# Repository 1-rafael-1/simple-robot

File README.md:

# simple-robot

A not-too-simple tracked robot with autonomous navigation and sensor-driven obstacle avoidance, written in Rust with Embassy. v2 reached the limits of its hardware platform; development continues in the follow-up [explorer-robot](https://github.com/1-rafael-1/explorer-robot) repository.

*Side view showing the robot's profile — the v2 iteration.*

## Project History

This started out as a hobby project for my 10-year-old son, who wanted me to build a robot for him. The thing started as a rather simple machine (v1) and then I got a little carried away. Check out the v1-robot navigating autonomously, download the demo video here: [Autonomous Operation](misc/media/autonomous-mode.mp4).

> Note: The initial version of this robot is preserved in the [`v1` tag](../../tree/v1). That version represents a simple but functional obstacle-avoiding robot using basic components. The v2 iteration described here is tagged [`v2`](../../tree/v2) and is now mothballed.

In v1, the robot could move autonomously by avoiding obstacles in a very simple way. That meant driving straight until an obstacle is detected, back up a little and then make a random turn. It was fun to watch and my son was happy with it.

v2 set out to be much more capable. The plan was to add spatial awareness through an IMU and a sweeping ultrasonic sensor, build more sophisticated autonomous navigation modes, and eventually integrate an AI camera module for follow-me and object-finding. Some of that worked out; some of it ran into hardware limits that couldn't be solved on this platform.

People have pointed out to me various things. The gist is that there are of course ready-made chassis solutions, ready-made RTOS for robotics and even probably complete systems available and that I am setting out to solve things that can be solved with much less effort by using existing things in code as well as hardware. This is all true and I do not dispute it. My motivation is different, though: I am not truly that much interested in having the actual robot, I have no use case at all for it, in fact. I just truly enjoy the process of building, figuring out how to do things, learning a ton of new stuff and it passes my rare spare time in a rewarding way.

## What v2 Achieved

The v2 firmware is a fully integrated platform built on Embassy async with a task-oriented architecture. A central orchestrator runs an event loop, dispatching sensor events to behavior handlers and UI updates. The drive subsystem uses a single-producer command queue with intents for distance drives, in-place rotations, and brake/coast settling — all with IMU-corrected feedback and ramp-down near targets. Mode-agnostic obstacle detection triggers emergency braking across all modes.

The robot carries a custom 4-layer PCB designed in KiCad, hand-soldered, with an RP2350 at 150 MHz. It drives four TT motors through two TB6612FNG motor drivers, reads four hall-effect encoders, and runs an ICM-20948 9-axis IMU with on-chip DMP sensor fusion. An HC-SR04 ultrasonic sensor on a servo performs 0–160° sweeps with a 30° cone correction algorithm, feeding a shared sweep buffer used by both the OLED's radar visualization and the autonomous navigation modes. Two front-facing IR sensors provide close-range collision detection, and a PCA9555 I2C port expander handles motor direction/standby pins and additional inputs. An RGB LED indicates battery state and obstacle alerts.

The UI is driven by an EC11 rotary encoder with push button and an SSD1306 OLED display. A menu system exposes hardware tests (motors, encoders, IMU, ultrasonic sweep, drive accuracy), calibration routines (motor speed, IMU, distance factor), and autonomous mode selection. Calibration data persists to flash storage.

Two autonomous modes are implemented:
- **Coast-and-avoid** — drives forward until an obstacle is detected, backs up, and turns a random angle. Simple but reliable.
- **Attempt straight line** — the user sets a target distance (100–1000 cm); the robot sweeps the ultrasonic sensor, performs gap analysis with drift correction, and navigates leg-by-leg toward the goal while avoiding obstacles.

Three side-quest crates were published along the way: [`hcsr04_async`](https://crates.io/crates/hcsr04_async) (async HC-SR04 driver), [`moving_median`](https://crates.io/crates/moving_median) (moving median filter), and [`icm20948-rs`](https://crates.io/crates/icm20948-rs) (ICM-20948 driver with DMP support).

## Why v2 Ends Here

The robot works, but it cannot reach the spatial awareness and navigation precision the original vision demanded. Several hard limits converge:

**Spatial awareness is the primary bottleneck.** The HC-SR04 ultrasonic sensor, even with servo sweeping and cone correction, is fundamentally imprecise. Its 30° detection cone could have been overcome algorithmically, but it produces false readings far too easily — a carpet, a floor tile seam, or a slightly textured surface registers as an obstacle. That makes reliable navigation impossible. The front-facing IR sensors work but have very short range and would require redesigning the sensor array holder to be truly useful. There is no downward-facing sensor to detect stairs or ledges.

**The board is out of pins.** The RP2350 on a Pico 2, even with a PCA9555 port expander, has every pin in use. There is no room to add a downward edge sensor, a better spatial sensor, or anything else. Some of those pins are spent on RC receiver inputs and a UART for an AI board that were never fully utilized, and on four motor encoders and two motor driver modules — overhead that a two-motor design would eliminate.

**Four TT motors reach a precision ceiling.** Two motors per track were necessary to move the Proto-Tank chassis, but that doubled the encoder and PWM pin count. The cheap hall-effect encoders and the inherent variability of TT motors mean no amount of calibration will deliver the positional accuracy needed for reliable dead-reckoning navigation.

**The I2C bus is shared** between the IMU, the OLED display, and the port expander. Motor direction changes go through the expander on that same bus. This never caused a hard failure in testing, but it is a fragile design with no headroom.

None of these are software problems. They are hardware constraints of a design that started from a simple tank chassis and grew organically. v2 went as far as it could on this platform.

## What's Next

Development continues in the follow-up **[explorer-robot](https://github.com/1-rafael-1/explorer-robot)** repository. I am not yet sure where this will go, but the plan is to build a more capable robot with better spatial awareness and navigation precision.

## Licensing Overview

This project uses multiple licenses depending on the component:

- **Firmware code** (`src/`, `build.rs`, `Cargo.toml`, etc.): Licensed under **MIT License** (see `LICENSE-MIT.md`)
- **3D-printed chassis designs** (`misc/chassis/`): Based on the Proto-Tank Chassis by fustyles, licensed under **CC BY-SA 4.0** (see attribution below)
- **Schematic and hardware design** (`misc/media/schematic_picture.png`): Licensed under **CC BY-SA 4.0** (see `LICENSE-CC-BY-SA-4.0.md`)
- **Documentation** (`docs/`, `README.md`): Licensed under **CC BY-SA 4.0**

Please review the individual license files and attribution sections for detailed information.

## Schematic

You can find the KiCad project here: [misc/KiCad/simple-robot](misc/KiCad/simple-robot). Some of the boards I used had no symbols & footprints and so I created them as I went. You can find them here: [misc/KiCad/symbols](misc/KiCad/symbols). The Pi Pico symbol I found online here: [ncarandini/KiCad-RP-Pico](https://github.com/ncarandini/KiCad-RP-Pico).

*The v2 schematic (current design)*

*The v2 PCB layout (current design)*

## 3D Printing

The robot chassis and various mounting components are designed to be 3D printed. I printed all parts in PLA and they worked quite okay so far. The 3D models are stored in the `misc/chassis` directory with both FreeCAD source files (.FCStd) and print-ready formats (.3mf, .stl).

For convenient printing with a Bambu Lab 3D printer, two Bambu Studio print projects are included:

- **print project.3mf** - Complete robot chassis assembly including the base frame, servo mount, HC-SR04 ultrasonic sensor mount, and IR sensor mounts
- **track pin print project.3mf** - Track pin components for securing and tensioning the robot's tracks (recently added)

The individual component files are also available if you prefer to customize your print settings:
- BaseFrame - edit.3mf/stl (main chassis frame)
- 9g servo mount.3mf (servo mounting bracket)
- hc-sr04 mount.3mf (ultrasonic sensor mount)
- IR Sensor mount.3mf (infrared sensor mounting)
- PCB mounting base.3mf (circuit board support)
- track pin.3mf (individual track pin component)

For more details on the chassis components, file formats, and assembly, see [misc/chassis/README.md](misc/chassis/README.md).

## Side quests that became necessary

Building the thing I found no async driver for the HC-SR04, so I had to make one myself:

- <https://github.com/1-rafael-1/hcsr04_async>
- Also on <https://crates.io/crates/hcsr04_async>.

This was fun :-)

Testing the ultrasonic sensor I found it gets even more unreliable when moving. So I searched for some moving median filtering solution, found none and made one myself:

- <https://github.com/1-rafael-1/moving_median>
- Also on <https://crates.io/crates/moving_median>

A little less fun.

I replaced the initial MPU9250/MPU6050 I never truly got to work with the ICM20948, a more modern 9-axis IMU from the same manufacturer (TDK InvenSense). The ICM20948 offers better performance and I created a driver for it:

- <https://github.com/1-rafael-1/ICM-20948-rs>
- Also on <https://crates.io/crates/icm20948-rs>

The driver supports async I2C operations and includes examples for RP2350. This was to a degree vibe-coded because that is truly out of my league, but it seems to work okay so far. I am sure there are many things that could be done better, but it is a start and I can now get good orientation data from the IMU, which is a big step forward for the project.

## The code

The code is written in Rust and makes heavy use of the Embassy framework. The architecture is task‑oriented, with a central orchestration loop handling events and routing them to behavior modules. Tasks stay resident and idle when not needed, which keeps the control flow predictable and makes it easy to evolve the system.

The drive subsystem is explicitly single‑producer/single‑executor: higher‑level modes build queues of drive steps, submit them to the drive queue executor, and await a single queue completion. Per‑step completion is internal to the executor, and interrupts remain available for preemption.

There are two modules, `system` and `task`. The `system` module contains rather general things like the event system and state. The `task` module contains the tasks that are run by the system.

### State Modules and Lock Order

The global state is split into domain-specific modules under `system/state/*` to reduce contention and keep hot paths lock-free where possible:

- `system/state/power.rs`
- `system/state/motion.rs`
- `system/state/perception.rs`
- `system/state/calibration.rs`

UI mode state lives in `task/ui/state.rs` (via `UI_STATE`) and is kept separate from the system state lock order.

When multiple state mutexes must be held at the same time, a uniform lock order is required to avoid deadlocks:

1. `POWER_STATE`
2. `CALIBRATION_STATE`
3. `PERCEPTION_STATE`
4. `MOTION_STATE`

The `main.rs` file is the entry point of the program but does nothing besides initializing some resources and then spawning all the tasks.

The firmware uses both cores of the RP2350 at the nominal 150 MHz clock speed: core0 runs the orchestrator, drive subsystem, sensors, and UI; core1 owns the I2C bus and runs the display, IMU, and port expander tasks. It uses a few percent of the flash space and about 20% of the RAM. The single I2C bus is shared between the IMU, the OLED display, and the port expander — this never caused issues in testing, but it is a tight design with no room for additional devices.

## Acknowledgments & Attribution

### Proto-Tank Chassis Design

The robot's tracked chassis is based on the [Proto-Tank](https://www.thingiverse.com/thing:972768) project, which is licensed under [Creative Commons Attribution 4.0 International](https://creativecommons.org/licenses/by/4.0/).

The Proto-Tank design has been modified and adapted for the simple-robot project to integrate custom motor mounts, PCB solutions, and sensor integration.

See [misc/chassis/ATTRIBUTION.md](misc/chassis/ATTRIBUTION.md) for full attribution details and license information.

## Disclaimer

I am a hobbyist, I have no formal electronics education and am still relatively new to the hobby (2.5 years now). I am also still as new to Rust and Embedded. By now I have a basic understanding of how things work and of what are higher level things in embedded. Enough for maker-level, far off from actual professional level. So expect imperfections.

I use AI when coding, which has proven to be an excellent teaching tool for learning a new language. It allows me to explore more advanced concepts than I could on my own, making self-teaching much easier than it was just a year or two ago. That being said: The code is my take on how to do this, actual professionals will find a thousand things one could do better. In case you find a thing that could be better: Happy to hear about it, get in touch! :-)

## Component Summary

The following is a summary of the components used in the v2 schematic (see [KiCad project](misc/KiCad/simple-robot)).

### Microcontroller

| Ref | Component | Notes |
|-----|-----------|-------|
| U1 | Raspberry Pi Pico 2 (RP2350) | Main controller |

### Sensors

| Ref | Component | Notes |
|-----|-----------|-------|
| I1 | ICM-20948 module | 9-axis IMU (accelerometer, gyroscope, magnetometer), I2C |
| J11 | HC-SR04 ultrasonic sensor | Connected via JST 4-pin, with servo sweeper |
| J12, J13 | IR obstacle detection sensors (×2) | Right-front and left-front |
| J14 | Grove Vision AI v2 | Camera/AI module, JST 4-pin |

### Motor Control

| Ref | Component | Notes |
|-----|-----------|-------|
| MD1, MD2 | TB6612FNG motor driver carriers (×2) | Left track & right track |
| J6–J9 | Motor encoders (×4) | LF, LR, RF, RR via JST 3-pin |
| J1, J2, J4, J5 | DC motor connectors (×4) | JST 2-pin |

### Communication & IO Expansion

| Ref | Component | Notes |
|-----|-----------|-------|
| P1 | PCA9555 I2C port expander | 16-bit GPIO expander |
| LS_1, LS_2, LS_3 | Bi-directional level shifters (×3) | 3.3V ↔ 5V |
| U2 | CD4049UB | Hex inverting buffer (DIP-16) |

### User Interface

| Ref | Component | Notes |
|-----|-----------|-------|
| OLED1 | SSD1306 OLED display module | I2C |
| SW1 | Rotary encoder with push switch | User input |
| LED1 | 5mm RGB LED (common cathode) | Status indicator |
| — | RF receiver | Remote control, via JST 3-pin |

### Power

| Ref | Component | Notes |
|-----|-----------|-------|
| B1 | LM2596 DC-DC buck converter module | Steps battery voltage down |
| J10 | Screw terminal (2-pin) | Battery input |
| D1, D3 | 1N5819 Schottky diodes (×2) | Power path protection |

### Passive Components

| Ref | Component | Notes |
|-----|-----------|-------|
| C2–C16, C19–C24, C26 | 100nF ceramic capacitors (×20) | Decoupling |
| C18 | 4700µF 16V electrolytic | Bulk decoupling (motors) |
| C1, C7 | 220µF polarized (×2) | |
| C17 | 220µF 10V | |
| C25 | 10µF 16V | |
| R2, R3 | 47Ω (×2) | |
| R5, R6 | 1kΩ (×2) | |
| R8 | 10kΩ | |
| R4, R7 | 20kΩ (×2) | |
| R10, R11 | 220Ω (×2) | LED current limiting |
| R9 | 330Ω | LED current limiting |

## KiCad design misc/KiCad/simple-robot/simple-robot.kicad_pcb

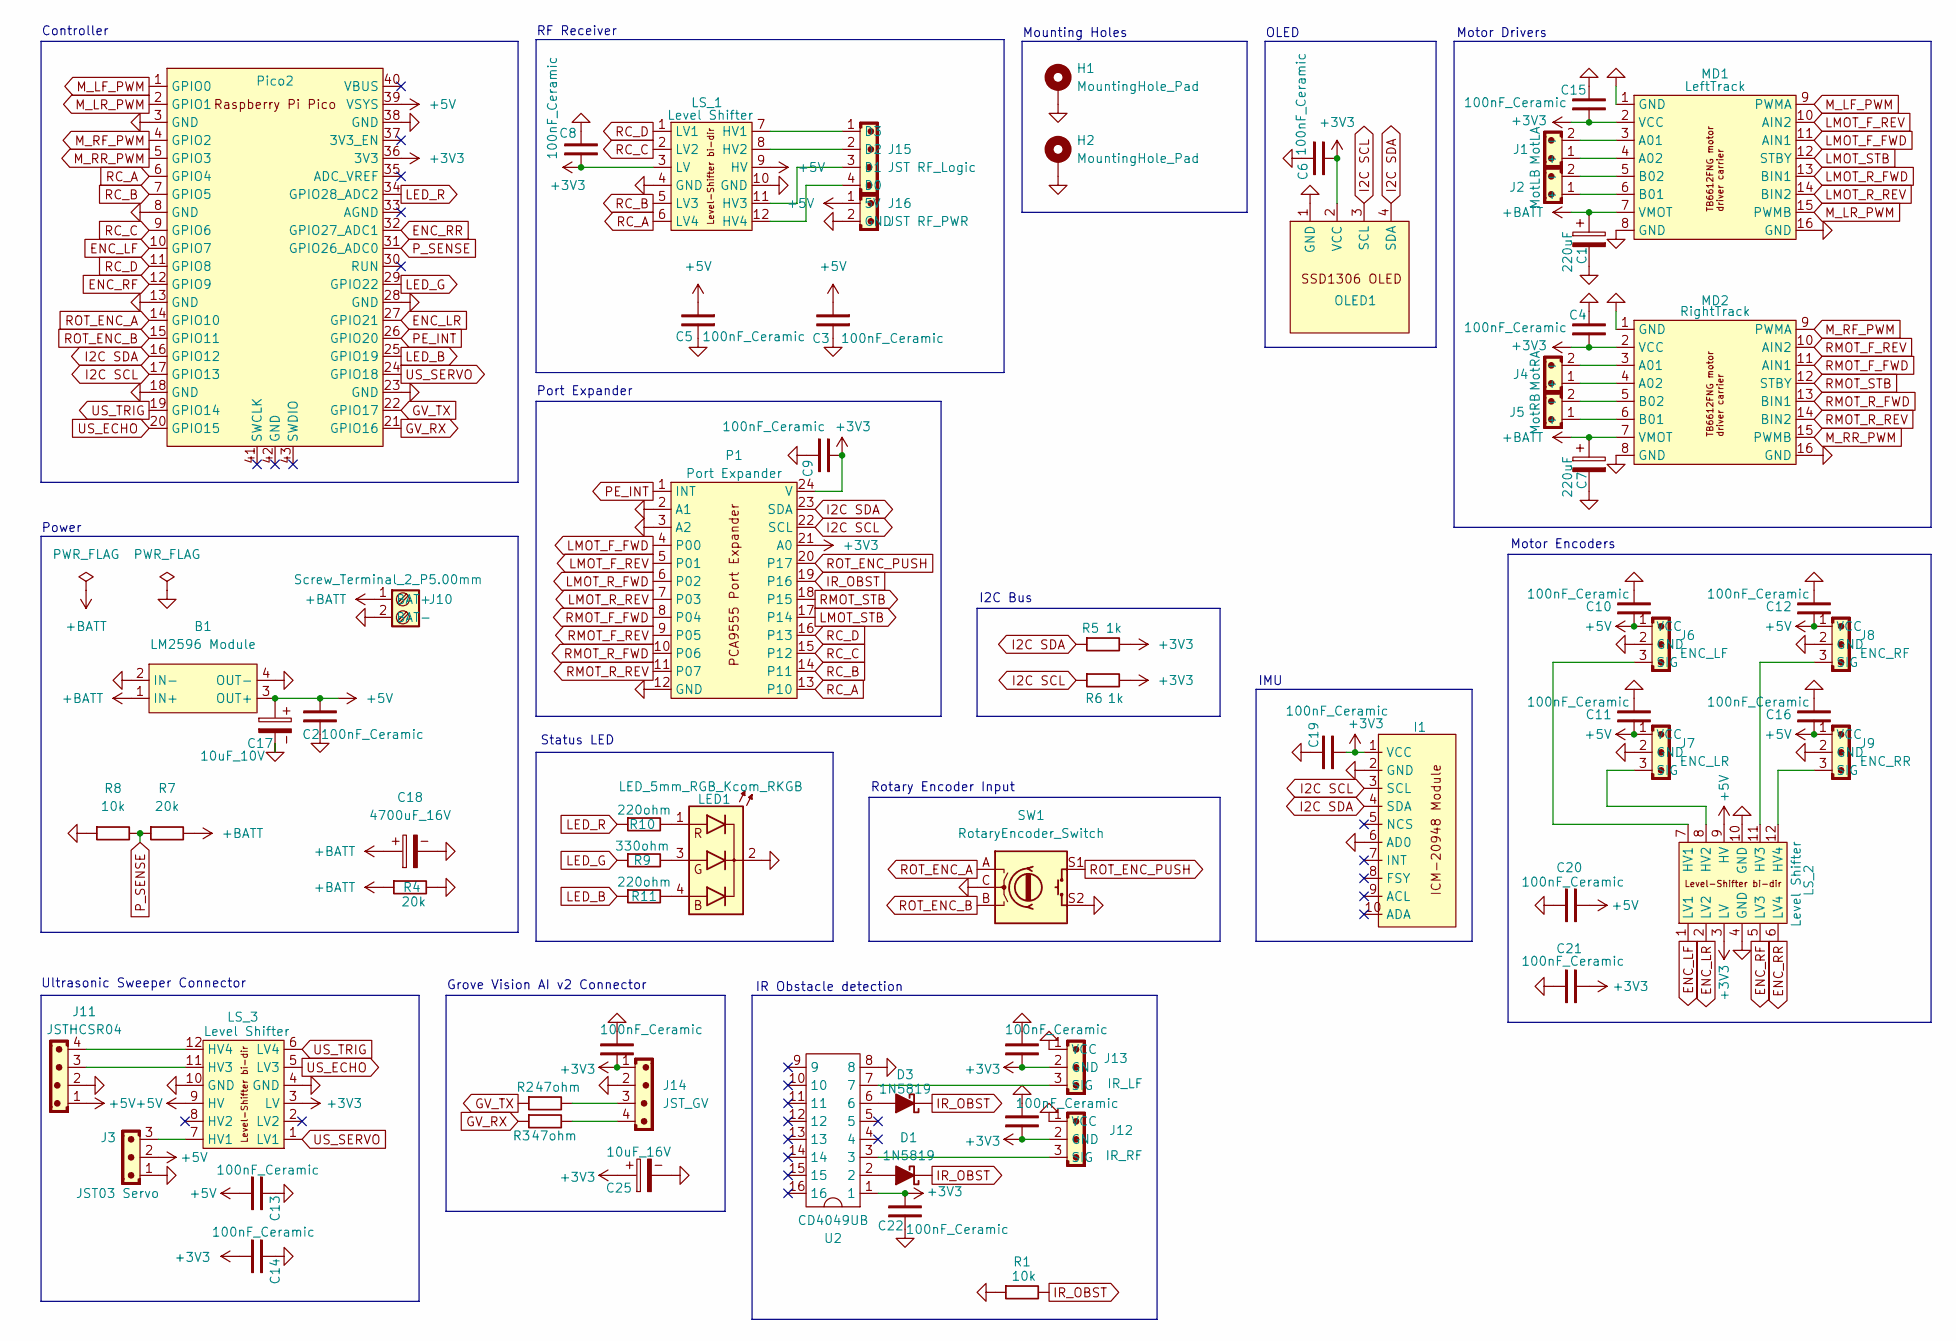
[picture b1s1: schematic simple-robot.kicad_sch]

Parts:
B1: LM2596 Module; LM2596_Module
C1, C7: 220uF; CP_Radial_D6.3mm_P2.50mm
C2, C3, C4, C5, C6, C8, C9, C10, C11, C12, C13, C14, C15, C16, C19, C20, C21, C22, C23, C24, C26: 100nF_Ceramic; C_Disc_D5.0mm_W2.5mm_P2.50mm
C17: 10uF_10V; CP_Radial_D6.3mm_P2.50mm
C18: 4700uF_16V; CP_Radial_D16.0mm_P7.50mm
C25: 10uF_16V; CP_Radial_D5.0mm_P2.00mm
D1, D3: 1N5819; D_DO-41_SOD81_P7.62mm_Horizontal
H1, H2: MountingHole_Pad; MountingHole_3.7mm_Pad_Via
I1: ICM-20948-module
J1: MotLA; JST_PH_B2B-PH-K_1x02_P2.00mm_Vertical
J2: MotLB; JST_PH_B2B-PH-K_1x02_P2.00mm_Vertical
J3: JST03 Servo; JST_EH_B3B-EH-A_1x03_P2.50mm_Vertical
J4: MotRA; JST_PH_B2B-PH-K_1x02_P2.00mm_Vertical
J5: MotRB; JST_PH_B2B-PH-K_1x02_P2.00mm_Vertical
J6: ENC_LF; JST_PH_B3B-PH-K_1x03_P2.00mm_Vertical
J7: ENC_LR; JST_PH_B3B-PH-K_1x03_P2.00mm_Vertical
J8: ENC_RF; JST_PH_B3B-PH-K_1x03_P2.00mm_Vertical
J9: ENC_RR; JST_PH_B3B-PH-K_1x03_P2.00mm_Vertical
J10: Screw_Terminal_2_P5.00mm; TerminalBlock_Phoenix_PT-1,5-2-5.0-H_1x02_P5.00mm_Horizontal
J11: JSTHCSR04; JST_EH_B4B-EH-A_1x04_P2.50mm_Vertical
J12: IR_RF; JST_PH_B3B-PH-K_1x03_P2.00mm_Vertical
J13: IR_LF; JST_PH_B3B-PH-K_1x03_P2.00mm_Vertical
J14: JST_GV; JST_EH_B4B-EH-A_1x04_P2.50mm_Vertical
J15: JST RF_Logic; JST_EH_B4B-EH-A_1x04_P2.50mm_Vertical
J16: JST RF_PWR; JST_EH_B2B-EH-A_1x02_P2.50mm_Vertical
LED1: LED_5mm_RGB_Kcom_RKGB; LED_D5.0mm-4_RGB_Wide_Pins
LS_1, LS_2, LS_3: Level Shifter; Level shifter 4 bi-dir
MD1: LeftTrack; TB6612FNG motor driver carrier
MD2: RightTrack; TB6612FNG motor driver carrier
OLED1: SSD1306
P1: Port Expander; PCA9555 Port Expander
R1, R8: 10k; R_Axial_DIN0207_L6.3mm_D2.5mm_P10.16mm_Horizontal
R2, R3: 47ohm; R_Axial_DIN0207_L6.3mm_D2.5mm_P10.16mm_Horizontal
R4, R7: 20k; R_Axial_DIN0207_L6.3mm_D2.5mm_P10.16mm_Horizontal
R5, R6: 1k; R_Axial_DIN0207_L6.3mm_D2.5mm_P10.16mm_Horizontal
R9: 330ohm; R_Axial_DIN0207_L6.3mm_D2.5mm_P10.16mm_Horizontal
R10, R11: 220ohm; R_Axial_DIN0207_L6.3mm_D2.5mm_P10.16mm_Horizontal
SW1: RotaryEncoder_Switch; RotaryEncoder_Alps_EC11E-Switch_Vertical_H20mm
U1: Pico2; raspberry_pi_pico_THT
U2: CD4049UB; DIP-16_W7.62mm_LongPads

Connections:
+3V3: C4.1, C6.2, C8.1, C9.2, C14.1, C15.1, C19.1, C21.2, C22.2, C23.1, C24.1, C25.1, C26.1, I1.1 (VCC), J12.2 (GND), J13.2 (GND), J14.1, LS_1.3 (LV), LS_2.3 (LV), LS_3.3 (LV), MD1.2 (VCC), MD2.2 (VCC), OLED1.2 (VCC), P1.21 (A0), P1.24 (V), R5.2, R6.2, U1.36 (3V3), U2.1
+5V: B1.3 (OUT+), C2.2, C3.1, C5.1, C10.1, C11.1, C12.1, C13.1, C16.1, C17.1, C20.2, J3.2, J6.1 (VCC), J7.1 (VCC), J8.1 (VCC), J9.1 (VCC), J11.1, J16.1 (5V), LS_1.9 (HV), LS_2.9 (HV), LS_3.9 (HV), U1.39 (VSYS)
+BATT: B1.1 (IN+), C1.1, C7.1, C18.1, J10.1 (BAT+), MD1.7 (VMOT), MD2.7 (VMOT), R4.1, R7.2
ENC_LF: LS_2.1 (LV1), U1.10 (GPIO7)
ENC_LR: LS_2.2 (LV2), U1.27 (GPIO21)
ENC_RF: LS_2.5 (LV3), U1.12 (GPIO9)
ENC_RR: LS_2.6 (LV4), U1.32 (GPIO27_ADC1)
GND: B1.2 (IN-), B1.4 (OUT-), C1.2, C2.1, C3.2, C4.2, C5.2, C6.1, C7.2, C8.2, C9.1, C10.2, C11.2, C12.2, C13.2, C14.2, C15.2, C16.2, C17.2, C18.2, C19.2, C20.1, C21.1, C22.1, C23.2, C24.2, C25.2, C26.2, H1.1, H2.1, I1.2 (GND), I1.6 (AD0), J3.1, J6.2 (GND), J7.2 (GND), J8.2 (GND), J9.2 (GND), J10.2 (BAT-), J11.2, J12.1 (VCC), J13.1 (VCC), J14.2, J16.2 (GND), LED1.2 (A), LS_1.4 (GND), LS_1.10 (GND), LS_2.4 (GND), LS_2.10 (GND), LS_3.4 (GND), LS_3.10 (GND), MD1.1 (GND), MD1.8 (GND), MD1.16 (GND), MD2.1 (GND), MD2.8 (GND), MD2.16 (GND), OLED1.1 (GND), P1.2 (A1), P1.3 (A2), P1.12 (GND), R1.1, R4.2, R8.1, SW1.C, SW1.S2, U1.3 (GND), U1.8 (GND), U1.13 (GND), U1.18 (GND), U1.23 (GND), U1.28 (GND), U1.38 (GND), U2.8
GV_RX: R3.1, U1.21 (GPIO16)
GV_TX: R2.1, U1.22 (GPIO17)
I2C SCL: I1.3 (SCL), OLED1.3 (SCL), P1.22 (SCL), R6.1, U1.17 (GPIO13)
I2C SDA: I1.4 (SDA), OLED1.4 (SDA), P1.23 (SDA), R5.1, U1.16 (GPIO12)
IR_OBST: D1.1 (K), D3.1 (K), P1.19 (P16), R1.2
LED_B: R11.1, U1.25 (GPIO19)
LED_G: R9.1, U1.29 (GPIO22)
LED_R: R10.1, U1.34 (GPIO28_ADC2)
LMOT_F_FWD: MD1.11 (AIN1), P1.4 (P00)
LMOT_F_REV: MD1.10 (AIN2), P1.5 (P01)
LMOT_R_FWD: MD1.13 (BIN1), P1.6 (P02)
LMOT_R_REV: MD1.14 (BIN2), P1.7 (P03)
LMOT_STB: MD1.12 (STBY), P1.17 (P14)
M_LF_PWM: MD1.9 (PWMA), U1.1 (GPIO0)
M_LR_PWM: MD1.15 (PWMB), U1.2 (GPIO1)
M_RF_PWM: MD2.9 (PWMA), U1.4 (GPIO2)
M_RR_PWM: MD2.15 (PWMB), U1.5 (GPIO3)
unnamed: D1.2 (A), U2.2
unnamed: D3.2 (A), U2.6
unnamed: J1.1 (+), MD1.4 (A02)
unnamed: J1.2 (-), MD1.3 (A01)
unnamed: J2.1 (+), MD1.6 (B01)
unnamed: J2.2 (-), MD1.5 (B02)
unnamed: J4.1 (+), MD2.4 (A02)
unnamed: J4.2 (-), MD2.3 (A01)
unnamed: J5.1 (+), MD2.6 (B01)
unnamed: J5.2 (-), MD2.5 (B02)
unnamed: J6.3 (SIG), LS_2.7 (HV1)
unnamed: J7.3 (SIG), LS_2.8 (HV2)
unnamed: J8.3 (SIG), LS_2.11 (HV3)
unnamed: J9.3 (SIG), LS_2.12 (HV4)
unnamed: J12.3 (SIG), U2.3
unnamed: J13.3 (SIG), U2.7
unnamed: J14.3, R2.2
unnamed: J14.4, R3.2
unnamed: J15.4 (D0), LS_1.12 (HV4)
unnamed: J15.3 (D1), LS_1.11 (HV3)
unnamed: J15.2 (D2), LS_1.8 (HV2)
unnamed: J15.1 (D3), LS_1.7 (HV1)
unnamed: LED1.4 (B), R11.2
unnamed: LED1.3 (G), R9.2
unnamed: LED1.1 (R), R10.2
unnamed: J3.3, LS_3.7 (HV1)
unnamed: J11.3, LS_3.11 (HV3)
unnamed: J11.4, LS_3.12 (HV4)
PE_INT: P1.1 (INT), U1.26 (GPIO20)
P_SENSE: R7.1, R8.2, U1.31 (GPIO26_ADC0)
RC_A: LS_1.6 (LV4), P1.13 (P10), U1.6 (GPIO4)
RC_B: LS_1.5 (LV3), P1.14 (P11), U1.7 (GPIO5)
RC_C: LS_1.2 (LV2), P1.15 (P12), U1.9 (GPIO6)
RC_D: LS_1.1 (LV1), P1.16 (P13), U1.11 (GPIO8)
RMOT_F_FWD: MD2.11 (AIN1), P1.8 (P04)
RMOT_F_REV: MD2.10 (AIN2), P1.9 (P05)
RMOT_R_FWD: MD2.13 (BIN1), P1.10 (P06)
RMOT_R_REV: MD2.14 (BIN2), P1.11 (P07)
RMOT_STB: MD2.12 (STBY), P1.18 (P15)
ROT_ENC_A: SW1.A, U1.14 (GPIO10)
ROT_ENC_B: SW1.B, U1.15 (GPIO11)
ROT_ENC_PUSH: P1.20 (P17), SW1.S1
US_SERVO: LS_3.1 (LV1), U1.24 (GPIO18)

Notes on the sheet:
IMU
Mounting Holes
Grove Vision AI v2 Connector
I2C Bus
Port Expander
Rotary Encoder Input
Motor Encoders
Ultrasonic Sweeper Connector
IR Obstacle detection
OLED
RF Receiver
Motor Drivers
Status LED
Controller
Power

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
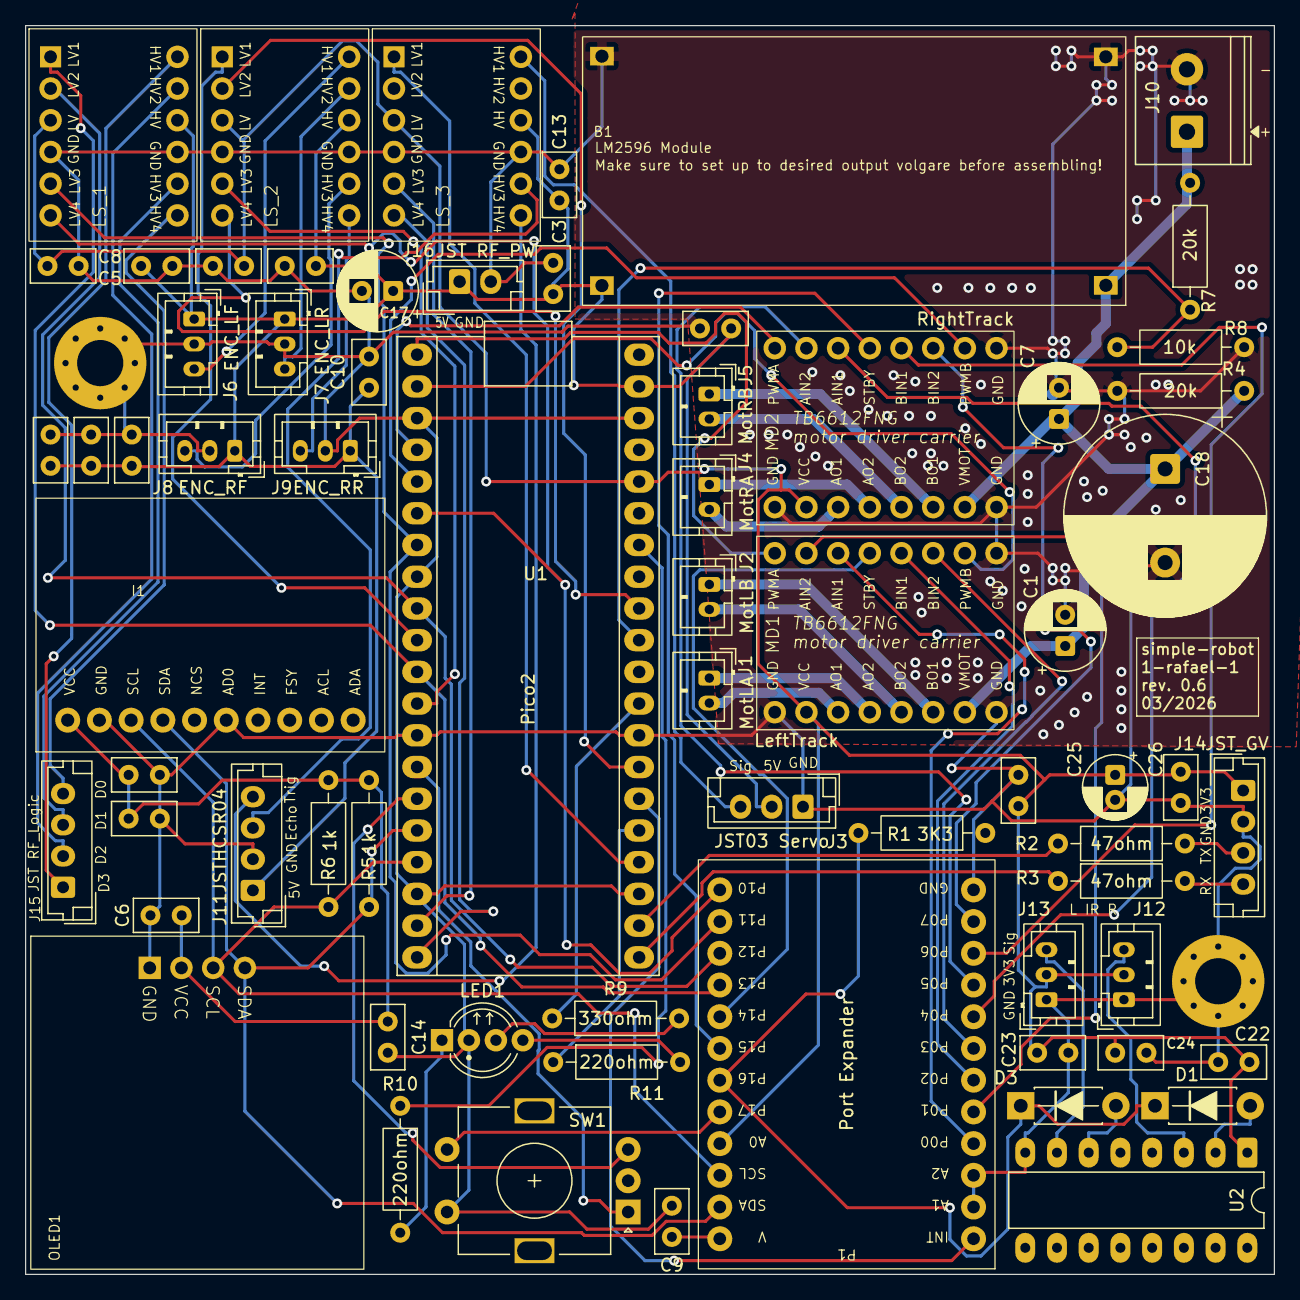
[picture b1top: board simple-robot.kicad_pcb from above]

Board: 4 copper layers, 100.0 x 100.0 mm, 70 parts (0 on the bottom side), 70 nets.

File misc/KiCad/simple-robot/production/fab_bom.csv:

Designator,Footprint,Quantity,Value,LCSC Part #
B1,LM2596_Module,1,LM2596 Module,
"C1, C7",CP_Radial_D6.3mm_P2.50mm,2,220uF,
"C10, C11, C12, C13, C14, C15, C16, C19, C2, C20, C21, C22, C23, C24, C26, C3, C4, C5, C6, C8, C9",C_Disc_D5.0mm_W2.5mm_P2.50mm,21,100nF_Ceramic,
C17,CP_Radial_D6.3mm_P2.50mm,1,10uF_10V,
C18,CP_Radial_D16.0mm_P7.50mm,1,4700uF_16V,
C25,CP_Radial_D5.0mm_P2.00mm,1,10uF_16V,
"D1, D3",D_DO-41_SOD81_P7.62mm_Horizontal,2,1N5819,
I1,ICM-20948-module,1,~,
J1,JST_PH_B2B-PH-K_1x02_P2.00mm_Vertical,1,MotLA,
J10,"TerminalBlock_Phoenix_PT-1,5-2-5.0-H_1x02_P5.00mm_Horizontal",1,Screw_Terminal_2_P5.00mm,
J11,JST_EH_B4B-EH-A_1x04_P2.50mm_Vertical,1,JSTHCSR04,
J12,JST_PH_B3B-PH-K_1x03_P2.00mm_Vertical,1,IR_RF,
J13,JST_PH_B3B-PH-K_1x03_P2.00mm_Vertical,1,IR_LF,
J14,JST_EH_B4B-EH-A_1x04_P2.50mm_Vertical,1,GV,
J15,JST_EH_B4B-EH-A_1x04_P2.50mm_Vertical,1,JST RF-LOG,
J16,JST_EH_B2B-EH-A_1x02_P2.50mm_Vertical,1,RF_PWR,
J2,JST_PH_B2B-PH-K_1x02_P2.00mm_Vertical,1,MotLB,
J3,JST_EH_B3B-EH-A_1x03_P2.50mm_Vertical,1,Servo,
J4,JST_PH_B2B-PH-K_1x02_P2.00mm_Vertical,1,MotRA,
J5,JST_PH_B2B-PH-K_1x02_P2.00mm_Vertical,1,MotRB,
J6,JST_PH_B3B-PH-K_1x03_P2.00mm_Vertical,1,ENC_LF,
J7,JST_PH_B3B-PH-K_1x03_P2.00mm_Vertical,1,ENC_LR,
J8,JST_PH_B3B-PH-K_1x03_P2.00mm_Vertical,1,ENC_RF,
J9,JST_PH_B3B-PH-K_1x03_P2.00mm_Vertical,1,ENC_RR,
LED1,LED_D5.0mm-4_RGB_Wide_Pins,1,LED_5mm_RGB_Kcom_RKGB,
"LS_1, LS_2, LS_3",Level shifter 4 bi-dir,3,Level Shifter,
MD1,TB6612FNG motor driver carrier,1,LeftTrack,
MD2,TB6612FNG motor driver carrier,1,RightTrack,
OLED1,SSD1306,1,~,
P1,PCA9555 Port Expander,1,Port Expander,
"R10, R11",R_Axial_DIN0207_L6.3mm_D2.5mm_P10.16mm_Horizontal,2,220ohm,
"R2, R3",R_Axial_DIN0207_L6.3mm_D2.5mm_P10.16mm_Horizontal,2,47ohm,
"R4, R7",R_Axial_DIN0207_L6.3mm_D2.5mm_P10.16mm_Horizontal,2,20k,
"R5, R6",R_Axial_DIN0207_L6.3mm_D2.5mm_P10.16mm_Horizontal,2,1k,
R8,R_Axial_DIN0207_L6.3mm_D2.5mm_P10.16mm_Horizontal,1,10k,
R9,R_Axial_DIN0207_L6.3mm_D2.5mm_P10.16mm_Horizontal,1,330ohm,
SW1,RotaryEncoder_Alps_EC11E-Switch_Vertical_H20mm,1,RotaryEncoder_Switch,
U2,DIP-16_W7.62mm_LongPads,1,CD4049UB,

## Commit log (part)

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2024-12-25 more aggressive motor locking, since we are alone using it. Better smoothing of encoder correction.
2025-01-01 Schematic & PCB v0.1
2025-01-09 Migrate embassy crates to stable versions and refactor I2C/ADC resource management
    • Update embassy deps to stable versions
    • Switch from git deps to crates.io
    • Reduce task arena size to 4096
    • Add I2C and ADC static mutexes
    • Rename IMU task for consistency
2025-01-11 update README, clean up the KiCad project a bit, minor refactoring
2025-01-11 redo all formatting
2025-01-16 update 3d models for hc-sr04 mount, update KiCad files, update schematic and PCB
2025-01-23 calibrated servo
2025-02-04 some tidying up, make us sweep controllable
2025-02-12 Invert IR sensor output handling and update debounce logic
2025-02-22 Update Cargo.toml to set edition to 2024
2025-12-28 Remove test-modules crate and update .gitignore
2025-12-28 Replace MPU6050 with ICM20948 and add AHRS (#8)
    * Replace MPU6050 with ICM20948 and add AHRS
    * changes after review
2026-01-01 Add 3D printed chassis and attribution
    Include FreeCAD sources, Bambu Studio print projects (.3mf), and
    print-ready .stl components for the robot chassis. Add original
    Proto-Tank files under misc/chassis/proto-tank plus ATTRIBUTION.md and
    LICENSE.txt to satisfy CC BY 4.0 requirements
2026-01-12 Include dev branch in CI workflow
2026-01-13 Refactor flash storage and init wiring
    Use Signal to return motor and IMU calibration data and add
    CalibrationKind/CalibrationDataKind enums. Unify flash commands
    (SaveData/GetData/LoadAll/EraseAll), reduce command queue size, and move
    to signaling API in motor_driver. Adjust init order: create I2C earlier,
    initialize port expander earlier, and rename interrupt pin parameters.
2026-01-13 Add encoder reading task for motor encoders
2026-01-14 Upgrade KiCad project and schematic files
2026-01-16 Add battery voltage monitoring and compensation
2026-01-17 Add CalibrationStatus event and display updates
2026-01-18 Add IMU calibration and mag interference data
    Add magnetometer interference fields to ImuCalibration and
    implement serialization/deserialization (108 bytes). Add Default
    impl. Add drive-side magnetometer helpers and channel, plus system
    state track speed fields. Forward loaded calibration to IMU task and
    auto-start now triggers IMU calibration
2026-01-22 Add testing task module for development
2026-01-25 Add encoder drift compensation module
    Introduce DRIFT_* constants in drive types and wire a new
    drive/compensation.rs implementing track averaging, speed-diff
    calculation and bounded compensation actions. Remove EncoderFeedback
    and ImuFeedback DriveCommand variants and register the compensation
    module in drive mod. Also apply small cleanups: simplify
    with_timeout to .ok(), tidy imu_read return expressions, and
2026-01-26 Group and reformat crate use statements
2026-02-01 Add string helper module for status text
    Provide status_text that converts &str to heapless::String<20>.
    Returns None and logs a warning if the input exceeds capacity.
2026-02-01 Add JST connectors, rename nets, update footprints
    Rename power net +VBAT to +BATT and label several previously
    unconnected nets (e.g. IR_OBST, GV_TX/GV_RX, Net-(D1-A), Net-(D3-A),
    and various Jx pins). Add JST RF_PWR (J16) and RF_Logic (J15)
    symbols to the schematic. Replace/adjust footprint and properties for
    the capacitor/MD1 component and update reference/value/metadata.
2026-02-07 pcb routing and some cleaning up; makingready for ordering the pcb mnufactured
2026-02-07 Make motors_stopped const and document Start
2026-02-07 Fix clippy warnings with telemetry_logs feature and remove outdated README paragraph
    - Add documentation to MAG_DIAG_LOG_INTERVAL_MS constant
    - Add documentation to IMU_LOOP_DIAG_LOG_INTERVAL_MS constant
    - Add documentation to log_mag_diagnostics function
    - Suppress clippy::cast_possible_truncation warnings for timestamp casts (u64 to u32 is intentional for modulo operations)
    - Remove outdated paragraph referencing deleted docs/PIN_ASSIGNMENTS.md file
    These changes fix CI failures when clippy runs with --all-features enabled.
2026-02-08 Run Clippy with default and all features (#16)
    * Run Clippy with default and all features
    Split clippy into two runs: default features (removed -A dead_code)
    and an --all-features run. Treat warnings as errors.
    * Clamp battery percent and use u8 in events
    Clamp battery percentage to [0,100], compute both an f32 for debug and
    a u8 event value (with clippy allows). Add doc comments for
2026-02-08 Dev into main (#18)
    * Port expander and pin redistribution (#11)
    * isolate few components to start with, comment the rest. Introduce new
    motor driver without tb6612fng driver, also use a new port expander for
    this.
    * Add flash-backed calibration storage
    Add sequential-storage and embedded-storage-async dependencies and use
2026-02-14 Add UI state and menu handling in orchestrator
2026-02-14 fixed the `show_line` truncation issue
2026-02-14 fixed the IMU status handling when calibration values load
2026-02-15 this is not a drama
2026-02-17 straight and curved drive commands with feedback
    Building on given drive command feedback system introducing straight and
    curved with feedback, simple revolution counts for now.
2026-02-17 review: unused mut
2026-02-21 Drive module tidying (#24)
    * Remove drive/control module and rewire references
    Delete drive/control submodule files and update imports/usages.
    Repointed drive::control::RotationState references to
    drive::rotation::RotationState,
    adjusted docs and types comments, and updated a test to use
    DriveAction::Coast.
2026-02-22 rp235x E9 erratum hitting: rotary encoder should be reffed to common GND (#25)
    * rp235x E9 erratum hitting: rotary encoder should be reffed to common GND
    instead of 3V3
    Pulldowns on RP235x only work on after stepping A4, all my boards are
    stepping A2. So thereference for the encoder should not be 3V3 because
    that we will need to pull down and that will latch on the RP.
    Workaround is to add pulldowns which i will do for now but a proper
2026-02-28 Update battery holder CAD and 3MF files
2026-02-28 Use PIO0 for ultrasonic sweep
    Swap PIO assignments so PIO0 handles the ultrasonic sweep and PIO1
    handles other PIO-based tasks. Rename local PIO variables
    (pio0_*/pio1_*)
    and remove the now-obsolete UltrasonicSweepPins struct. Update
    ultrasonic
    servo pin mapping.
2026-02-28 debounce encoder turning
2026-03-01 some lints
2026-03-01 Testing tweaks (#31)
    * enter into menu on boot
    * debounce encoder turning
    * wrong register for button press on port expander
    * style of menu selection improved and more intuitive turning direction
    for te encoder.
    * calibration ui flow 1
2026-03-03 obstacle detection should blink the indicator
2026-03-06 do not use us measurement >200cm
2026-03-06 clearer naming for test modes
2026-03-06 add ultrasonic into the obstacle detection
2026-03-07 extract motion data from system state, also move track speeds to atomics
2026-03-08 normalize mag and accel
2026-03-08 Rework imu calibration (#35)
    * reworking imu calibration as three separate actions and make mag
    calibration more usable
    * normalize mag and accel
    * clippy was sad
    * copilot review
    * add 6axis fusion testmode. attempt to get magnetometer calibrated, so
2026-03-16 Enable Git integration in KiCad project
2026-03-16 Use per-request reply slot for drive queue
    Replace global DRIVE_QUEUE_COMPLETIONS with a per-request reply slot
    guarded by an AtomicBool-backed DriveQueueReplyGuard. Acquire drains any
    stale completion before use and ensures the slot is released on drop.
    DriveQueueRequest now carries the reply_channel reference.
2026-03-29 introduce idle, brake and coast as drive intents, so that we can enqueue these into the overall drive queue system
2026-05-16 fix broken nets on pcb
    swapping of trigger and echo pins was incomplete on pcb nets
    update to recent KiCad version
2026-05-16 try if cargo will install toolchain
2026-05-16 Bump version, handle legacy IMU key, fix IMU axes
    Keep legacy IMU key (1) so the flash scanner can skip pre-DMP
    120-byte records without aborting scans. Restore current ImuCalibration
    to key 3 and document both schemas. Swap DMP roll/pitch mapping to
    match the robot body frame (sensor axes differ)
2026-06-07 refine drive control: implement better compensation on stationary turns and correct straight motion only by imu. also split the test modes into distint turn, straight, arc.
2026-06-08 add skills
2026-06-09 Replace constant torque ladder with proportional speed control
2026-06-09 Suppress clippy lint and derive Default for CalibrationData
2026-06-09 Fix queue status handling for concurrent cancellations and failures
2026-06-10 Fix coast and avoid (#43)
    * Fix queue status handling for concurrent cancellations and failures
    * Increase obstacle detection threshold to 13 cm
    * Reduce obstacle detection threshold and improve re-avoidance logic
    Increase ultrasonic obstacle threshold from 13 cm to 15 cm. Refactor
    avoidance maneuver to loop until path is clear, using turn-only
    re-attempts with opposite direction and fresh sensor checks after each
2026-06-18 Refactor drive task: extract dispatch, replace drift loop with inline correction
2026-06-18 Refactor and deepen drive module (#45)
    * Deepen perception module with atomic obstacle flags and private mutex
    Migrate obstacle detection state to lock-free atomic flags, keeping
    ultrasonic readings behind a private mutex exposed via accessors.
    Consolidate duplicated reset/clear logic into dedicated API methods.
    - Add `AtomicBool` flags for IR, ultrasonic, and combined detection
    - Introduce `ChangeDetected` enum for setter return values
2026-06-19 Derive Debug, Clone, Copy for ImuReadings and simplify getter
2026-06-19 Consolidate IMU sensor state into a single struct (#47)
    * Consolidate IMU sensor state into a single struct
    Replace six separate `LATEST_*` statics and their individual accessors
    with a
    single `LATEST_READINGS` mutex containing a new `ImuReadings` struct.
    Expose
    all fields through a unified `get_latest_readings()` async function,
2026-06-20 Refactor sensor data flow to point-to-point channels
    Replace the event-based sensor routing with direct channels between
    sensor tasks and the drive subsystem. Remove the now-unnecessary
    sensor event variants and the motion/sensor_events behavior modules.
    Consolidate IMU start/stop calls to direct function invocations instead
    of raising events through the orchestrator. Update ultrasonic sweep
    handling to write perception state directly from the sensor task.
2026-06-20 Migrate UI event dispatch to async send and expand channel capacity
    Refactor the orchestrator to call `send_ui_event` instead of
    `try_send_ui_event`, removing the silent-drop fallback. Increase the
    UI event channel capacity from 8 to 64 so the async sender never
    blocks in practice.
    Extract `render_autonomous_running_from_values` to let the autonomous
    refresh tick re-use its cached perception snapshot, avoiding redundant
2026-06-20 Stabilze obstacle detection (#50)
    * Update resistor value from 10k to 3K3 and bump KiCad project revision to
    6
    * Add coast-avoid detection test and raise obstacle threshold to 20 cm
    - Add CoastAvoidDetection test mode to verify
    IR→perception→EmergencyBrake chain
    - Raise ultrasonic obstacle threshold from 15 cm to 20 cm for better
